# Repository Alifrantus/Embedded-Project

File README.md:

Báo cáo môn Hệ thống Nhúng của Nhóm 8 - Lớp 169290

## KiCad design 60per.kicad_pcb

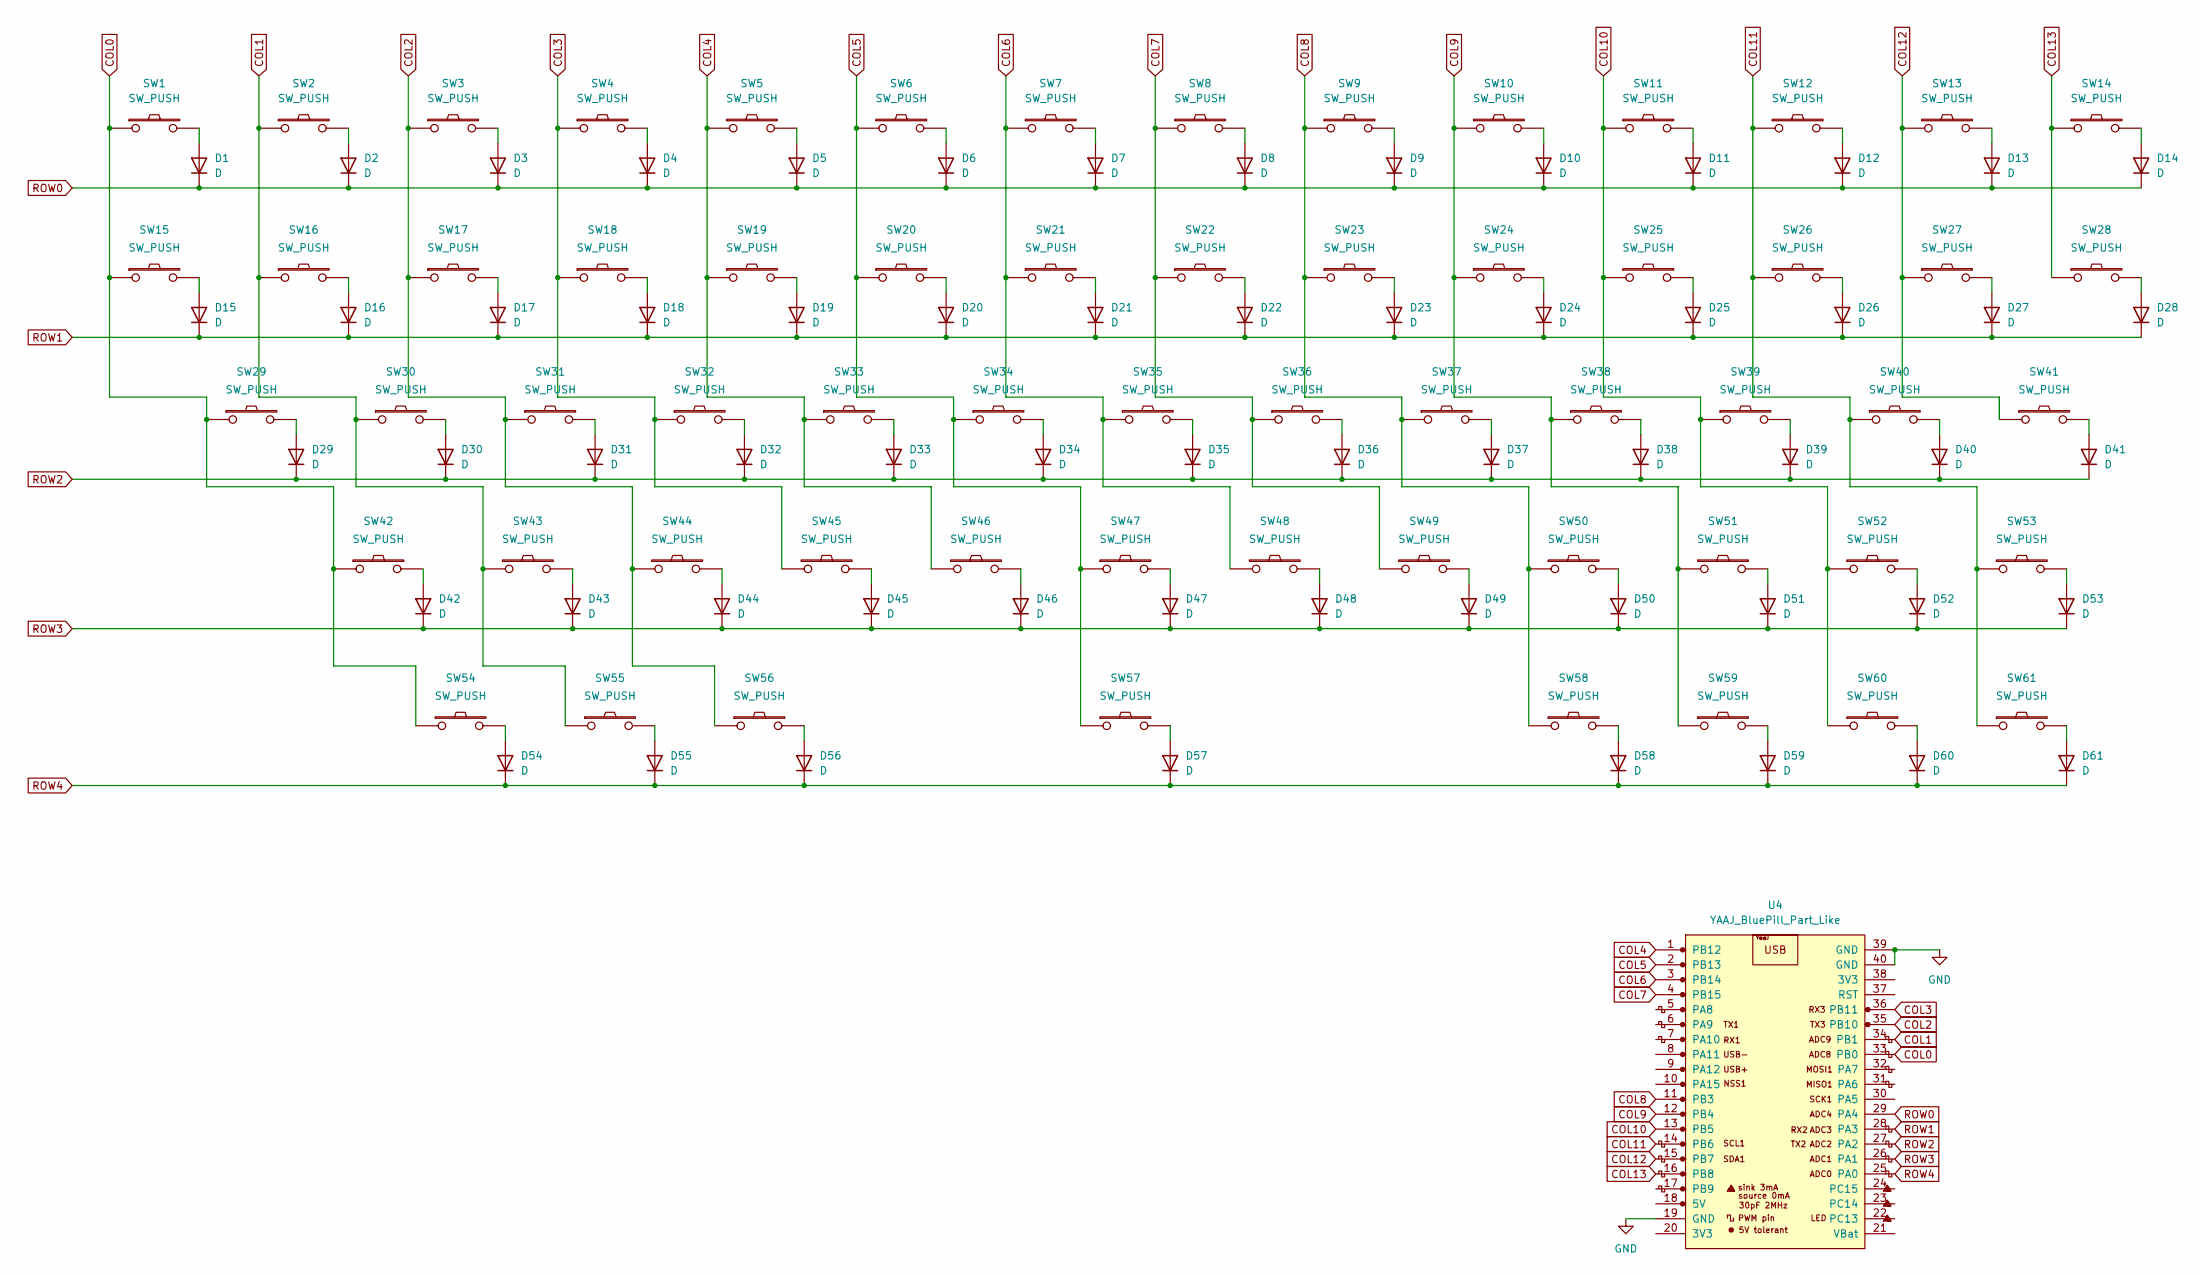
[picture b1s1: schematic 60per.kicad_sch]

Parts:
D1, D2, D3, D4, D5, D6, D7, D8, D9, D10, D11, D12, D13, D14, D15, D16, D17, D18, D19, D20, D21, D22, D23, D24, D25, D26, D27, D28, D29, D30, D31, D32, D33, D34, D35, D36, D37, D38, D39, D40, D41, D42, D43, D44, D45, D46, D47, D48, D49, D50, D51, D52, D53, D54, D55, D56, D57, D58, D59, D60, D61: D; D_1206_3216Metric
SW1, SW2, SW3, SW4, SW5, SW6, SW7, SW8, SW9, SW10, SW11, SW12, SW13, SW16, SW17, SW18, SW19, SW20, SW21, SW22, SW23, SW24, SW25, SW26, SW27, SW30, SW31, SW32, SW33, SW34, SW35, SW36, SW37, SW38, SW39, SW40, SW43, SW44, SW45, SW46, SW47, SW48, SW49, SW50, SW51, SW52: SW_PUSH; SW_Cherry_MX_PCB_1.00u
SW14: SW_PUSH; SW_Cherry_MX_PCB_2.00u
SW15, SW28: SW_PUSH; SW_Cherry_MX_PCB_1.50u
SW29: SW_PUSH; SW_Cherry_MX_PCB_1.75u
SW41, SW42: SW_PUSH; SW_Cherry_MX_PCB_2.25u
SW53: SW_PUSH; SW_Cherry_MX_PCB_2.75u
SW54, SW55, SW56, SW58, SW59, SW60, SW61: SW_PUSH; SW_Cherry_MX_PCB_1.25u
SW57: SW_PUSH; SW_Cherry_MX_PCB_6.25u
U4: YAAJ_BluePill_Part_Like; YAAJ_BluePill_2

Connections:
COL0: SW1.1, SW15.1, SW29.1, SW42.1, SW54.1, U4.33 (PB0)
COL1: SW2.1, SW16.1, SW30.1, SW43.1, SW55.1, U4.34 (PB1)
COL2: SW3.1, SW17.1, SW31.1, SW44.1, SW56.1, U4.35 (PB10)
COL3: SW4.1, SW18.1, SW32.1, SW45.1, U4.36 (PB11)
COL4: SW5.1, SW19.1, SW33.1, SW46.1, U4.1 (PB12)
COL5: SW6.1, SW20.1, SW34.1, SW47.1, SW57.1, U4.2 (PB13)
COL6: SW7.1, SW21.1, SW35.1, SW48.1, U4.3 (PB14)
COL7: SW8.1, SW22.1, SW36.1, SW49.1, U4.4 (PB15)
COL8: SW9.1, SW23.1, SW37.1, SW50.1, SW58.1, U4.11 (PB3)
COL9: SW10.1, SW24.1, SW38.1, SW51.1, SW59.1, U4.12 (PB4)
COL10: SW11.1, SW25.1, SW39.1, SW52.1, SW60.1, U4.13 (PB5)
COL11: SW12.1, SW26.1, SW40.1, SW53.1, SW61.1, U4.14 (PB6)
COL12: SW13.1, SW27.1, SW41.1, U4.15 (PB7)
COL13: SW14.1, SW28.1, U4.16 (PB8)
GND: U4.19 (GND), U4.39 (GND), U4.40 (GND)
unnamed: D1.2 (A), SW1.2
unnamed: D2.2 (A), SW2.2
unnamed: D3.2 (A), SW3.2
unnamed: D4.2 (A), SW4.2
unnamed: D5.2 (A), SW5.2
unnamed: D6.2 (A), SW6.2
unnamed: D7.2 (A), SW7.2
unnamed: D8.2 (A), SW8.2
unnamed: D9.2 (A), SW9.2
unnamed: D10.2 (A), SW10.2
unnamed: D11.2 (A), SW11.2
unnamed: D12.2 (A), SW12.2
unnamed: D13.2 (A), SW13.2
unnamed: D14.2 (A), SW14.2
unnamed: D15.2 (A), SW15.2
unnamed: D16.2 (A), SW16.2
unnamed: D17.2 (A), SW17.2
unnamed: D18.2 (A), SW18.2
unnamed: D19.2 (A), SW19.2
unnamed: D20.2 (A), SW20.2
unnamed: D21.2 (A), SW21.2
unnamed: D22.2 (A), SW22.2
unnamed: D23.2 (A), SW23.2
unnamed: D24.2 (A), SW24.2
unnamed: D25.2 (A), SW25.2
unnamed: D26.2 (A), SW26.2
unnamed: D27.2 (A), SW27.2
unnamed: D28.2 (A), SW28.2
unnamed: D29.2 (A), SW29.2
unnamed: D30.2 (A), SW30.2
unnamed: D31.2 (A), SW31.2
unnamed: D32.2 (A), SW32.2
unnamed: D33.2 (A), SW33.2
unnamed: D34.2 (A), SW34.2
unnamed: D35.2 (A), SW35.2
unnamed: D36.2 (A), SW36.2
unnamed: D37.2 (A), SW37.2
unnamed: D38.2 (A), SW38.2
unnamed: D39.2 (A), SW39.2
unnamed: D40.2 (A), SW40.2
unnamed: D41.2 (A), SW41.2
unnamed: D42.2 (A), SW42.2
unnamed: D43.2 (A), SW43.2
unnamed: D44.2 (A), SW44.2
unnamed: D45.2 (A), SW45.2
unnamed: D46.2 (A), SW46.2
unnamed: D47.2 (A), SW47.2
unnamed: D48.2 (A), SW48.2
unnamed: D49.2 (A), SW49.2
unnamed: D50.2 (A), SW50.2
unnamed: D51.2 (A), SW51.2
unnamed: D52.2 (A), SW52.2
unnamed: D53.2 (A), SW53.2
unnamed: D54.2 (A), SW54.2
unnamed: D55.2 (A), SW55.2
unnamed: D56.2 (A), SW56.2
unnamed: D57.2 (A), SW57.2
unnamed: D58.2 (A), SW58.2
unnamed: D59.2 (A), SW59.2
unnamed: D60.2 (A), SW60.2
unnamed: D61.2 (A), SW61.2
ROW0: D1.1 (K), D2.1 (K), D3.1 (K), D4.1 (K), D5.1 (K), D6.1 (K), D7.1 (K), D8.1 (K), D9.1 (K), D10.1 (K), D11.1 (K), D12.1 (K), D13.1 (K), D14.1 (K), U4.29 (PA4)
ROW1: D15.1 (K), D16.1 (K), D17.1 (K), D18.1 (K), D19.1 (K), D20.1 (K), D21.1 (K), D22.1 (K), D23.1 (K), D24.1 (K), D25.1 (K), D26.1 (K), D27.1 (K), D28.1 (K), U4.28 (PA3)
ROW2: D29.1 (K), D30.1 (K), D31.1 (K), D32.1 (K), D33.1 (K), D34.1 (K), D35.1 (K), D36.1 (K), D37.1 (K), D38.1 (K), D39.1 (K), D40.1 (K), D41.1 (K), U4.27 (PA2)
ROW3: D42.1 (K), D43.1 (K), D44.1 (K), D45.1 (K), D46.1 (K), D47.1 (K), D48.1 (K), D49.1 (K), D50.1 (K), D51.1 (K), D52.1 (K), D53.1 (K), U4.26 (PA1)
ROW4: D54.1 (K), D55.1 (K), D56.1 (K), D57.1 (K), D58.1 (K), D59.1 (K), D60.1 (K), D61.1 (K), U4.25 (PA0)

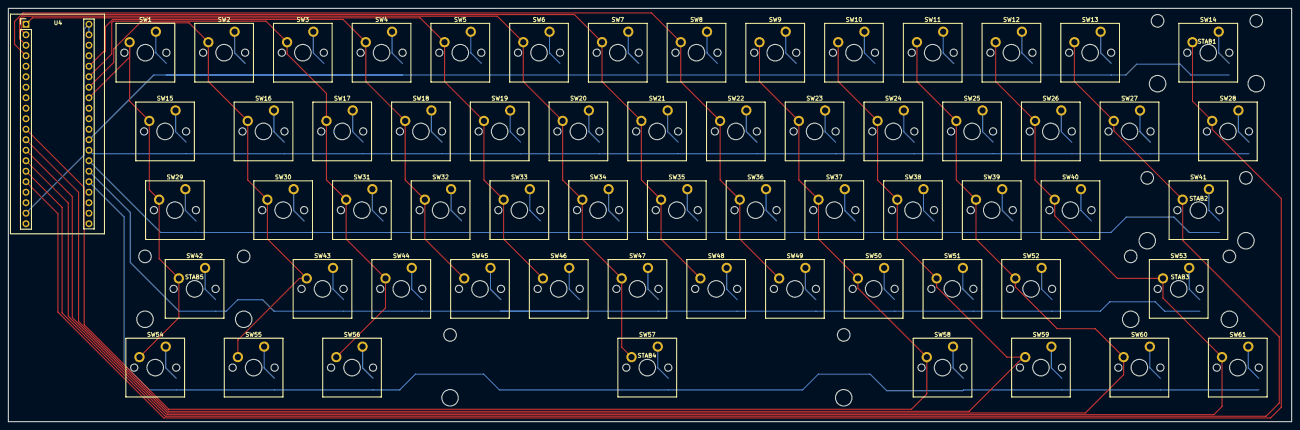
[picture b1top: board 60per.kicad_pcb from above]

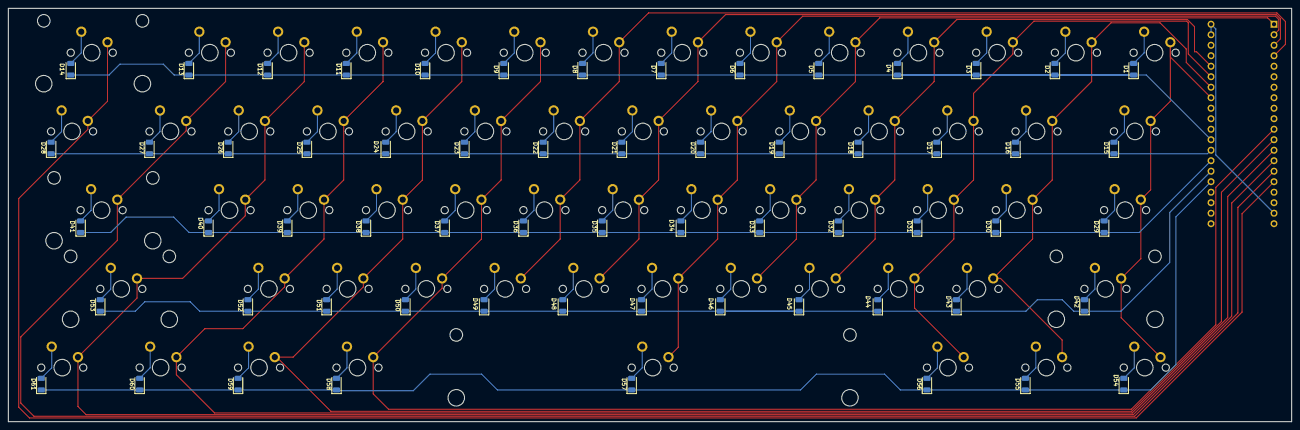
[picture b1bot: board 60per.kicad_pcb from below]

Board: 2 copper layers, 310.5 x 100.0 mm, 128 parts (61 on the bottom side), 81 nets.

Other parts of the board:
STAB1, STAB2, STAB3, STAB5: Stabilizer_Cherry_MX_2.00u
STAB4: Stabilizer_Cherry_MX_6.00u

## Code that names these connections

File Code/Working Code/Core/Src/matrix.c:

#include "matrix.h"
#include "stm32f1xx_hal.h"

/* ============================================================
 *  PIN MAPPING — thực tế theo dây hàn trên PCB
 *
 *  ROW PINS : GPIOA → OUTPUT Push-Pull, Active LOW
 *  COL PINS : GPIOB → INPUT Pull-Up,    LOW = nhấn
 *
 *  Row mapping (đếm từ dưới lên):
 *    Hàng 1 (Ctrl/Space) = PA0 → keymap row 4
 *    Hàng 2 (Shift/Z)    = PA1 → keymap row 3
 *    Hàng 3 (Caps/A)     = PA2 → keymap row 2
 *    Hàng 4 (Tab/Q)      = PA3 → keymap row 1
 *    Hàng 5 (số)         = PA4 → keymap row 0
 *
 *  Col mapping (thứ tự GPIO theo dây hàn thực tế):
 *    col[ 0] → PB0   col[ 7] → PB15
 *    col[ 1] → PB1   col[ 8] → PB3
 *    col[ 2] → PB10  col[ 9] → PB4
 *    col[ 3] → PB11  col[10] → PB5
 *    col[ 4] → PB12  col[11] → PB6
 *    col[ 5] → PB13  col[12] → PB7
 *    col[ 6] → PB14  col[13] → PB8
 *
 *  Sơ đồ nối:
 *    ROW(OUT) ── 1N4148(Cathode→ROW) ── Switch ── COL(IN PULLUP)
 * ============================================================ */

uint8_t matrix_raw[ROWS][COLS];

/* Row pins — thứ tự theo keymap row 0–4, PA pin đảo ngược */
static GPIO_TypeDef* const row_ports[ROWS] = {
    GPIOA, GPIOA, GPIOA, GPIOA, GPIOA
};
static const uint16_t row_pins[ROWS] = {
    GPIO_PIN_4,  /* row 0 — hàng số   (hàng 5 vật lý) → PA4 */
    GPIO_PIN_3,  /* row 1 — hàng Tab  (hàng 4 vật lý) → PA3 */
    GPIO_PIN_2,  /* row 2 — hàng Caps (hàng 3 vật lý) → PA2 */
    GPIO_PIN_1,  /* row 3 — hàng Shft (hàng 2 vật lý) → PA1 */
    GPIO_PIN_0,  /* row 4 — hàng Ctrl (hàng 1 vật lý) → PA0 */
};

/* Col pins — thứ tự theo col logic 0–13, GPIO pin theo dây hàn */
static GPIO_TypeDef* const col_ports[COLS] = {
    GPIOB, GPIOB, GPIOB, GPIOB, GPIOB, GPIOB, GPIOB,
    GPIOB, GPIOB, GPIOB, GPIOB, GPIOB, GPIOB, GPIOB
};
static const uint16_t col_pins[COLS] = {
    GPIO_PIN_0,   /* col 0  → PB0  */
    GPIO_PIN_1,   /* col 1  → PB1  */
    GPIO_PIN_10,  /* col 2  → PB10 */
    GPIO_PIN_11,  /* col 3  → PB11 */
    GPIO_PIN_12,  /* col 4  → PB12 */
    GPIO_PIN_13,  /* col 5  → PB13 */
    GPIO_PIN_14,  /* col 6  → PB14 */
    GPIO_PIN_15,  /* col 7  → PB15 */
    GPIO_PIN_3,   /* col 8  → PB3  */
    GPIO_PIN_4,   /* col 9  → PB4  */
    GPIO_PIN_5,   /* col 10 → PB5  */
    GPIO_PIN_6,   /* col 11 → PB6  */
    GPIO_PIN_7,   /* col 12 → PB7  */
    GPIO_PIN_8,   /* col 13 → PB8  */
};

/* ============================================================
 *  matrix_init — set tất cả row HIGH (inactive)
 * ============================================================ */
void matrix_init(void) {
    for (int r = 0; r < ROWS; r++) {
        HAL_GPIO_WritePin(row_ports[r], row_pins[r], GPIO_PIN_SET);
    }
}

/* ============================================================
 *  matrix_scan — quét toàn bộ 5×14
 *
 *  Mỗi row:
 *    1. Kéo row xuống LOW
 *    2. Chờ ~1µs settle
 *    3. Đọc 14 col: LOW = nhấn → raw = 1
 *    4. Khôi phục row lên HIGH
 * ============================================================ */
void matrix_scan(void) {
    for (int r = 0; r < ROWS; r++) {
        HAL_GPIO_WritePin(row_ports[r], row_pins[r], GPIO_PIN_RESET);

        /* ~1µs @ 72MHz */
        for (volatile int d = 0; d < 72; d++);

        for (int c = 0; c < COLS; c++) {
            matrix_raw[r][c] =
                (HAL_GPIO_ReadPin(col_ports[c], col_pins[c]) == GPIO_PIN_RESET)
                ? 1 : 0;
        }

        HAL_GPIO_WritePin(row_ports[r], row_pins[r], GPIO_PIN_SET);
    }
}

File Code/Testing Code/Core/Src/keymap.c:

#include "keymap.h"

/* Bản đồ phím 2 hàng x 2 cột */
const uint8_t keymap[NUM_LAYERS][ROWS][COLS] = {
    {
        /* COL0 (PB1)     COL1 (PB0) */
        {  KC_A,         KC_B  },    /* ROW0 (PB11): Nút 1 và Nút 2 */
        {  KC_C,         KC_D  }     /* ROW1 (PB10): Nút 3 và Nút 4 */
    }
};

uint8_t keymap_get(uint8_t layer, uint8_t row, uint8_t col) {
    if (layer >= NUM_LAYERS || row >= ROWS || col >= COLS) return KC_NO;
    return keymap[layer][row][col];
}

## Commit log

2026-06-10 Schematic & Layout
2026-06-10 Move files & add file code
2026-06-10 Removed excess files & add code
2026-06-10 Added images
2026-06-23 Added Working Code + Fixing folders names
2026-06-26 Adding README to the repo
2026-06-26 Added report files
